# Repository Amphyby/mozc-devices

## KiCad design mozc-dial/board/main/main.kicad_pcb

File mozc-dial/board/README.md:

# Board Assembly Guide

For the entire keyboard assembly, please refer to the [Build Guide](../buildguide.md).

## Common to All Editions

### Sensor Board (per board)

#### Bill of Materials

| Ref | Description | Qty | Notes |
|---|---|---|---|
| R1,R3,R5 | Resistor 330Ω | 3 | Through-hole or surface-mount |
| R2,R4,R6 | Not populated | - | |
| U1-3 | Reflective photo sensor RPR-220 | 3 | (e.g., [Reflective Photo Sensor (Photoreflector) RPR-220](https://akizukidenshi.com/catalog/g/g111401/)) |
| J1 | 2.54mm pitch 1x5 pin header | 1 | L-shaped is desirable (e.g., [Pin Header (Male L-type) 1x40 (40P)](https://akizukidenshi.com/catalog/g/g101627/)) |

#### Assembly

This explanation covers the case where all 3 bits are populated. However, for the 9-dial edition, some sensors may only require 1 or 2 bits. In that case, populate only the required number of components from the top (U1). For details, follow the instructions for the 9-dial edition.

Also, before making everything, it is recommended to check if the Gray code plate values can be read properly to reduce rework in case of problems. If it doesn't work well, populate resistors on R2, R4, and R6. For details, see [Reading Sensor Adjustment](#reading-sensor-adjustment).

First, attach the photo sensors from the side where the U1, U2, and U3 markings are visible. Pay close attention to the orientation. The upper right corner is chamfered, so check the marking and the shape of the sensor to ensure they are in the same orientation. After correct placement, cut off the excess leads from the back and solder them.

On the back side, there are places to attach three resistors on the `(SENSOR)` side and three on the `(LED)` side, as shown in the figure. Both through-hole and chip resistors can be used, so use the parts of your choice. However, even for through-hole types, it is more stable to mount them without passing them through the holes when attaching the dial.

As for the resistors, it depends on the adjustment as mentioned above. By default, we recommended using the internal pull-up, leaving the `(SENSOR)` side unpopulated and installing a 330Ω resistor on the `(LED)` side. However, since the internal resistance value varies greatly from device to device, we now recommend using the `no_pull` variant of the firmware, with 33KΩ on the `(SENSOR)` side and 330Ω on the `(LED)` side.

For the 1x5 pin header, using an L-shaped one will fit well in the case.

During assembly, pay attention to the `⇧Center` mark. The inner circumference of the dial will be in the direction of the arrow.

## 1-Dial Edition

This is an introductory edition that uses commercially available general-purpose parts other than the sensor board.

### Parts

- Raspberry Pi Pico: 1
- Sensor board (3-bit populated): 2
- [Unipolar Stepping Motor 28BYJ-48 5V](https://akizukidenshi.com/catalog/g/g113256/): 1
- [Stepping Motor Drive Module [M2003S]](https://www.aitendo.com/product/12366): 1
- Wiring materials: as needed

### Assembly

#### Sensor Board

Assemble two 3-bit populated sensor boards as described in the common section for all dial editions. We will call one `SENSOR L` and the other `SENSOR H`.

Although not a clean example as it was used for experiments, here are examples of mounting both through-hole and chip resistors.

Each board's pin header has five terminals: `V`, `1`, `2`, `3`, and `G`.
Of these, `V` connects to the 3.3V power supply, but the Raspberry Pi Pico we are using has only one 3.3V output terminal. Therefore, connect the terminal pair where `V` passes on the board, as shown by the red wiring in the photo.
In the diagram for the sensor board, the terminals inside the rectangle labeled `V`, that is, the six outer locations of the resistor patterns, are `V`.

The upper sensor board is `SENSOR L` for the inner circumference, and the lower sensor board is `SENSOR H` for the outer circumference.
Since `V` is interconnected, the `V` at the top-most, inner-most terminal is not needed for this connection.

#### Stepping Motor Drive Module

The Raspberry Pi Pico's GPIO cannot drive the motor directly, so the 1-dial edition uses a commercially available drive module. Any sink-type driver other than the one specified here will work, and you can also build your own by referring to the circuit of the 9-dial edition.

Taking the one mentioned here as an example, `IN1` to `IN4` enclosed in green are the terminals that receive the outputs `1` to `4` from the Raspberry Pi Pico. `GND` enclosed in black and `VCC` enclosed in red are `G` and `V` respectively.
The motor draws 5V power from the USB bus via the Raspberry Pi Pico. It requires about 0.3A, so the firmware for the 1-dial edition requests the 0.5A upper limit for USB micro.

The white terminal is used for connection with the stepping motor.

#### Raspberry Pi Pico

Attach L-shaped pin headers to a commercially available Raspberry Pi Pico as shown in the photo.
The three DEBUG pins at the bottom of the photo are optional and only needed if you need to develop and debug the firmware.

The pins used in the 1-dial edition are assigned as shown in the diagram. Connect to SENSOR L, SENSOR H, and MOTOR according to this diagram. When debugging, the standard output is output from TX via UART.

### Firmware Flashing

Follow the general method for the Raspberry Pi Pico. Connect the Raspberry Pi Pico to your PC while holding down the `BOOT` button on the board. A drive named `RPI-RP2` will appear. Copy `firmware/prebuilt/one_dial.uf2` into this drive. If the flashing is successful, the drive will disappear. Your OS may show a warning, but this is not a problem. From now on, when you connect this device to your PC without holding down the `BOOT` button, it will be recognized as a USB keyboard.

## 9-Dial Edition

### Parts

- Main board: 1
- Sensor board (3-bit populated): 6
- Sensor board (2-bit populated): 4
- Sensor board (1-bit populated): 1
- [Unipolar Stepping Motor 28BYJ-48 5V](https://akizukidenshi.com/catalog/g/g113256/): 9
- Wiring materials: as needed

### Main Board

#### Bill of Materials

| Ref | Description | Qty | Notes |
|---|---|---|---|
| C101 | Capacitor 10uF | 1 | |
| C102-121,C202-208,C212,C302-308,C312 | Capacitor 100nF | 36 | |
| C201,C209,C301,C309 | Capacitor 1uF | 4 | |
| C210,C211,C310,C311 | Capacitor 20pF | 4 | |
| J102-103 | 2.54mm pitch 1x3 pin header | 2 | |
| J106-J125 | 2.54mm pitch 1x5 pin header | 20 | |
| J201,J301 | USB TYPE C Receptacle | 2 | |
| R201-202,R301-302 | Resistor 27.4Ω | 4 | |
| R203-204,R303-304 | Resistor 5.1KΩ | 4 | |
| R205,R207,R305,R307 | Resistor 1KΩ | 4 | |
| R206,R306 | Resistor 10KΩ | 2 | |
| SW101,SW201,SW301 | Switch | 3 | |
| U101 | AMS1117 3.3V Regulator | 1 | |
| U102-103,U105,U107,U109 | TBD62083AFNG | 5 | |
| U104,U106,U108,U110 | 74HC238 | 4 | |
| U201,U301 | RP2040 | 2 | |
| U202,U302 | W25Q128JVS | 2 | |
| Y201,Y301 | 12MHz Crystal Oscillator | 2 | |
| N/A | Jumper pin | 2 | |

#### Assembly

The Gerber data for the main board is in `board/gerber/main.zip`. Together with `main_bom.csv` and `main_positions.csv`, this data can be used to order board manufacturing and assembly from JLCPCB. If you order correctly, you will receive a semi-finished board like the one below.

### Assembly

Attach 1x5 L-shaped pin headers for connecting to the sensor boards to `SENSOR A-L`, `SENSOR A-H`, `SENSOR B`, `SENSOR C`, `SENSOR D`, `SENSOR E`, `SENSOR F`, `SENSOR G`, `SENSOR H`, `SENSOR I-L`, and `SENSOR I-H`.

Attach 1x5 L-shaped pin headers for connecting to the motors to `MOTOR A`, `MOTOR B`, `MOTOR C`, `MOTOR D`, `MOTOR E`, `MOTOR F`, `MOTOR G`, `MOTOR H`, and `MOTOR I`.

If you attach them facing outwards on the front side like this, it will be easier to route the cables during wiring. It is a good idea to not insert the inner pins all the way, but to leave them slightly raised to create a height difference. Be especially careful with `SENSOR I-H`, which will pass over the USB connector.

The following work on the back side can minimize the board thickness and at the same time avoid short circuits with components and heat dissipation problems.

Attach a 1x3 pin header to the location marked `U1 PWR U2` and short the `U1` and `PWR` positions with a jumper pin.

Attach a 1x3 pin header to the location marked `USB V_MTR ALT` and short the `USB` and `V_MTR` positions with a jumper pin.

### Sensor Board

Referring to the [Common to All Dial Editions](#common-to-all-dial-editions) section, prepare a total of 11 sensor boards with the following populated bit widths. There is no problem other than an increase in standby power consumption if you populate more bits, so it is also fine to prepare all of them with a 3-bit width.

| Ref | Populated Bit Width |
|---|---|
| SENSOR A-L | 3 |
| SENSOR A-H | 3 |
| SENSOR B | 2 |
| SENSOR C | 3 |
| SENSOR D | 2 |
| SENSOR E | 3 |
| SENSOR F | 3 |
| SENSOR G | 2 |
| SENSOR H | 2 |
| SENSOR I-L | 3 |
| SENSOR I-H | 1 |

### Firmware Flashing

This dedicated board also follows the general method for Raspberry Pi Pico, but since two RP2040s are mounted on the board, you need to flash two firmwares to each.

First, flash the sub-chip using the USB Type-C terminal labeled `USB 2`. The jumper labeled `U1 PWR U2` normally shorts `U1` and `PWR`. This is a setting where the power on the board is taken from the `USB 1` terminal. Temporarily change this to short `PWR` and `U2`.

In this state, connect the `USB 2` terminal to the PC while holding down `BOOT 2`. Copy `sub.uf2` or `sub_no_pull.uf2` to the drive named `RPI-RP2` that appears on the PC. If the writing is successful, the drive will disappear.

Once disconnect from the PC, and then flash the main firmware. Return the jumper setting to shorting `U1` and `PWR`, and connect the `USB 1` terminal to the PC while holding down `BOOT 1`. Similarly, copy `main.uf2` or `main_no_pull.uf2`. When the drive disappears, the flashing is complete.

## Photo Sensor Adjustment

The photo sensor readings should not vary greatly as they are taken inside the case, but differences may arise due to the brightness of the 3D printing material or the quality of the paper on which the Gray code is printed. If the dial reading is unstable or the rotation does not stop, the sensor value change range may not be within the expected range. In that case, please adjust the sensor paying attention to the following points.

### Reading with RP2040

The sensor value is processed as a digital value by GPIO. Therefore, it needs to be adjusted so that HIGH is in the range of 2.0 - 3.3[V] and LOW is in the range of 0.0 - 0.3[V] when operating at 3.3V.

### LED Sensor Adjustment

If the current flowing through the LED is small, the light emission will be weak, and the amount of light read by the sensor will be insufficient. This will result in higher readings, and the voltage difference between white and black will not be clear. In that case, try changing the three resistors on the `(LED)` side to weaker ones. The standard is adjusted with 330Ω, but with the photo sensor RPR-220 used this time, it will stay within the rated value even if you lower it to about 40Ω. However, it will greatly affect the standby power consumption, so if possible, please adjust with the resistor on the reading sensor side.

### Reading Sensor Adjustment

You can shift the read voltage value by changing the pull-up resistance of the reading sensor. However, if you change it too much, the voltage difference between white and black will become less clear. You can adjust it by populating the three resistors on the `(SENSOR)` side. The standard firmware expects a pull-up of about 50-80KΩ by the RP2040's pull-up. If the voltage does not rise sufficiently with black, it is better to pull-up more strongly with an additional resistor. By following the [Firmware Development Guide](../firmware/README.md) and disabling the RP2040's pull-up, the resistor populated here will become the pull-up resistor. If you do not disable it, it will be pulled up by the combined resistance in parallel. The calculation is a bit complicated, but it may be easier to pull-up in parallel with an additional resistor without changing the firmware if you want to pull-up more strongly.

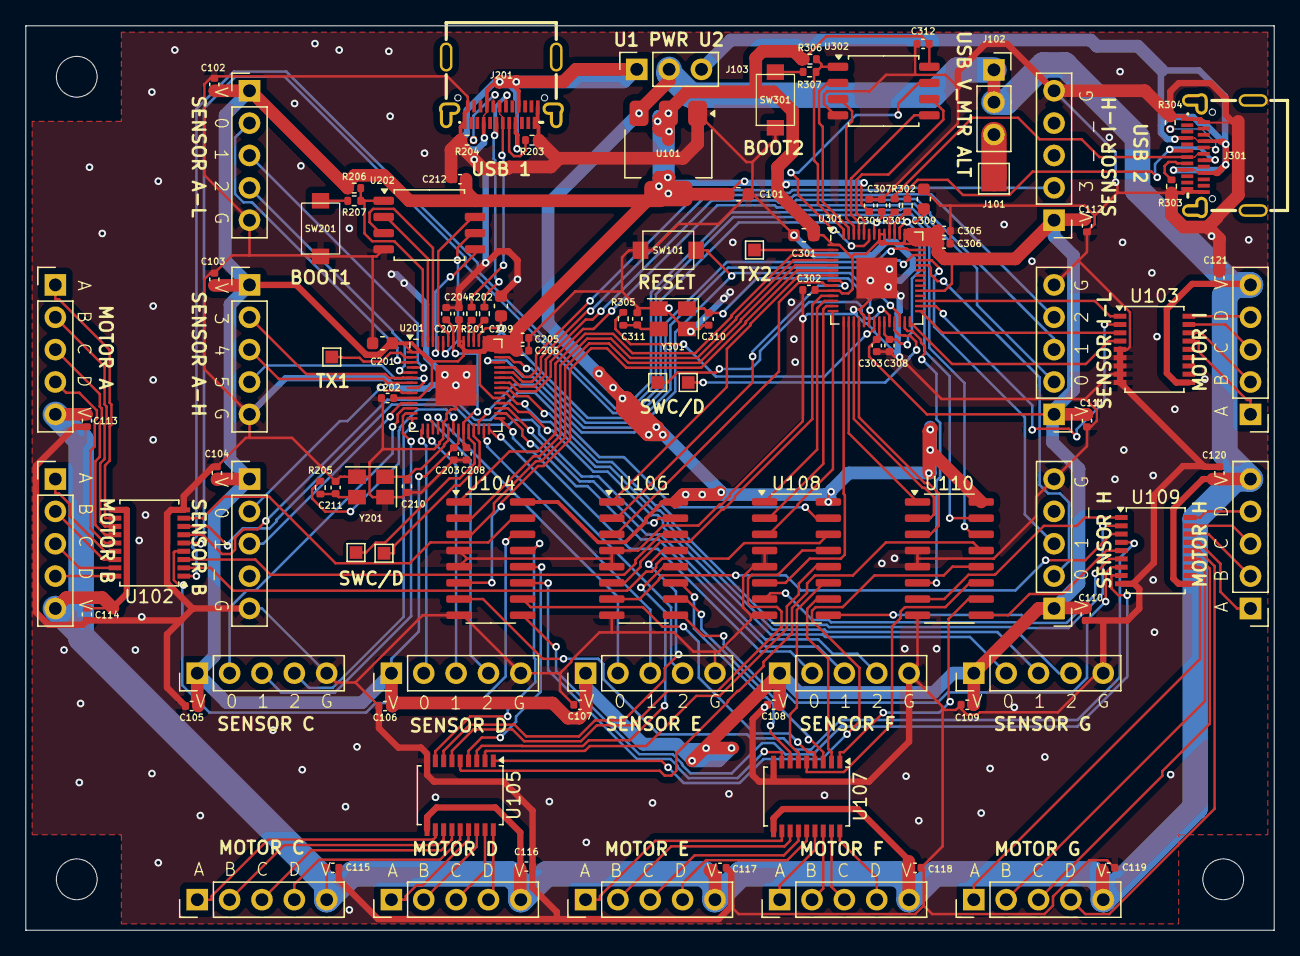
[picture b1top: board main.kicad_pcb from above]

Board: 2 copper layers, 98.0 x 71.0 mm, 112 parts (0 on the bottom side), 165 nets.

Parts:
C101: 10u; C_0603_1608Metric
C102, C103, C104, C105, C106, C107, C108, C109, C110, C111, C112, C113, C114, C115, C116, C117, C118, C119, C120, C121, C202, C203, C204, C205, C206, C207, C208, C212, C302, C303, C304, C305, C306, C307, C308, C312: 100n; C_0402_1005Metric
C201, C209, C301, C309: 1u; C_0603_1608Metric
C210, C211, C310, C311: 20p; C_0402_1005Metric
J101: Conn_01x01; TestPoint_Pad_2.0x2.0mm
J102, J103: Conn_01x03; PinSocket_1x03_P2.54mm_Vertical
J104, J105, J202, J203, J302, J303: Conn_01x01; TestPoint_Pad_1.0x1.0mm
J106, J107, J108, J109, J110, J111, J112, J113, J114, J115, J116, J117, J118, J119, J120, J121, J122, J123, J124, J125: Conn_01x05_Pin; PinHeader_1x05_P2.54mm_Vertical
J201, J301: USB_C_Receptacle; USBC_24P
R201, R202, R301, R302: 27.4; R_0402_1005Metric
R203, R204, R303, R304: 5.1K; R_0402_1005Metric
R205, R207, R305, R307: 1K; R_0402_1005Metric
R206, R306: 10K; R_0402_1005Metric
REF1, REF2, REF3: MountingHole_3.2mm_M3
SW101, SW201, SW301: SW_Push; SW_SMD_PUSH
U101: AMS1117-3.3; SOT-223-3_TabPin2
U102, U103, U105, U107, U109: TBD62083AFNG; SSOP-18_4.4x6.5mm_P0.65mm
U104, U106, U108, U110: 74HC238; SOP-16_3.9x9.9mm_P1.27mm
U201, U301: RP2040; QFN-56-1EP_7x7mm_P0.4mm_EP3.2x3.2mm
U202, U302: W25Q128JVS; SOIC-8_5.3x5.3mm_P1.27mm
Y201, Y301: 12MHz_GND24; Crystal_SMD_SeikoEpson_TSX3225-4Pin_3.2x2.5mm

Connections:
+1V1: C207.1, C208.1, C209.1, C307.1, C308.1, C309.1, U201.23 (DVDD), U201.45 (VREG_VOUT), U201.50 (DVDD), U301.23 (DVDD), U301.45 (VREG_VOUT), U301.50 (DVDD)
+3V3: C101.1, C102.1, C103.1, C104.1, C105.1, C106.1, C107.1, C108.1, C109.1, C110.1, C111.1, C112.1, C201.1, C202.1, C203.1, C204.1, C205.1, C206.1, C212.1, C301.1, C302.1, C303.1, C304.1, C305.1, C306.1, C312.1, J114.1, J115.1, J116.1, J117.1, J118.1, J120.1, J121.1, J122.1, J123.1, J124.1, J125.1, R206.1, R306.1, U101.2 (VO), U201.1 (IOVDD), U201.10 (IOVDD), U201.22 (IOVDD), U201.33 (IOVDD), U201.42 (IOVDD), U201.43 (ADC_AVDD), U201.44 (VREG_IN), U201.48 (USB_VDD), U201.49 (IOVDD), U202.8 (VCC), U301.1 (IOVDD), U301.10 (IOVDD), U301.22 (IOVDD), U301.33 (IOVDD), U301.42 (IOVDD), U301.43 (ADC_AVDD), U301.44 (VREG_IN), U301.48 (USB_VDD), U301.49 (IOVDD), U302.8 (VCC)
+5V: C113.1, C114.1, C115.1, C116.1, C117.1, C118.1, C119.1, C120.1, C121.1, J102.1, J102.2, J103.2, J106.5, J107.5, J108.5, J109.5, J110.5, J111.5, J112.5, J113.5, J119.5, U101.3 (VI), U102.10 (COMMON), U103.10 (COMMON), U104.16 (VCC), U105.10 (COMMON), U106.16 (VCC), U107.10 (COMMON), U108.16 (VCC), U109.10 (COMMON), U110.16 (VCC)
/I2C_SCL: U201.41 (GPIO29_ADC3), U301.41 (GPIO29_ADC3)
/I2C_SDA: U201.40 (GPIO28_ADC2), U301.40 (GPIO28_ADC2)
/MTRA_0: U102.8 (I8), U104.15 (Y0)
/MTRA_1: U102.4 (I4), U104.14 (Y1)
/MTRA_2: U104.13 (Y2), U105.8 (I8)
/MTRA_3: U104.12 (Y3), U105.4 (I4)
/MTRA_4: U104.11 (Y4), U107.8 (I8)
/MTRA_5: U104.10 (Y5), U107.4 (I4)
/MTRA_6: U104.9 (Y6), U109.8 (I8)
/MTRA_7: U104.7 (Y7), U109.4 (I4)
/MTRA_8: U103.4 (I4), U301.28 (GPIO17)
/MTRB_0: U102.7 (I7), U106.15 (Y0)
/MTRB_1: U102.3 (I3), U106.14 (Y1)
/MTRB_2: U105.7 (I7), U106.13 (Y2)
/MTRB_3: U105.3 (I3), U106.12 (Y3)
/MTRB_4: U106.11 (Y4), U107.7 (I7)
/MTRB_5: U106.10 (Y5), U107.3 (I3)
/MTRB_6: U106.9 (Y6), U109.7 (I7)
/MTRB_7: U106.7 (Y7), U109.3 (I3)
/MTRB_8: U103.3 (I3), U301.29 (GPIO18)
/MTRC_0: U102.6 (I6), U108.15 (Y0)
/MTRC_1: U102.2 (I2), U108.14 (Y1)
/MTRC_2: U105.6 (I6), U108.13 (Y2)
/MTRC_3: U105.2 (I2), U108.12 (Y3)
/MTRC_4: U107.6 (I6), U108.11 (Y4)
/MTRC_5: U107.2 (I2), U108.10 (Y5)
/MTRC_6: U108.9 (Y6), U109.6 (I6)
/MTRC_7: U108.7 (Y7), U109.2 (I2)
/MTRC_8: U103.2 (I2), U301.30 (GPIO19)
/MTRD_0: U102.5 (I5), U110.15 (Y0)
/MTRD_1: U102.1 (I1), U110.14 (Y1)
/MTRD_2: U105.5 (I5), U110.13 (Y2)
/MTRD_3: U105.1 (I1), U110.12 (Y3)
/MTRD_4: U107.5 (I5), U110.11 (Y4)
/MTRD_5: U107.1 (I1), U110.10 (Y5)
/MTRD_6: U109.5 (I5), U110.9 (Y6)
/MTRD_7: U109.1 (I1), U110.7 (Y7)
/MTRD_8: U103.1 (I1), U301.31 (GPIO20)
/RESET: SW101.2, U201.26 (RUN), U301.26 (RUN)
/RP2040_1/QSPI_SCLK: U201.52 (QSPI_SCLK), U202.6 (CLK)
/RP2040_1/QSPI_SD0: U201.53 (QSPI_SD0), U202.5 (DI/IO_{0})
/RP2040_1/QSPI_SD1: U201.55 (QSPI_SD1), U202.2 (DO/IO_{1})
/RP2040_1/QSPI_SD2: U201.54 (QSPI_SD2), U202.3 (~WP/IO_{2})
/RP2040_1/QSPI_SD3: U201.51 (QSPI_SD3), U202.7 (~HOLD/~RESET/IO_{3})
/RP2040_1/QSPI_SS: R206.2, R207.2, U201.56 (QSPI_SS), U202.1 (~CS)
/RP2040_1/SWCLK: J202.1, U201.24 (SWCLK)
/RP2040_1/SWD: J203.1, U201.25 (SWD)
/RP2040_1/USB_DM: J201.A7 (D-), J201.B7 (D-), R202.1
/RP2040_1/USB_DP: J201.A6 (D+), J201.B6 (D+), R201.1
/RP2040_1/VBUS: J103.1, J201.A4 (VBUS), J201.A9 (VBUS), J201.B4 (VBUS), J201.B9 (VBUS)
/RP2040_2/QSPI_SCLK: U301.52 (QSPI_SCLK), U302.6 (CLK)
/RP2040_2/QSPI_SD0: U301.53 (QSPI_SD0), U302.5 (DI/IO_{0})
/RP2040_2/QSPI_SD1: U301.55 (QSPI_SD1), U302.2 (DO/IO_{1})
/RP2040_2/QSPI_SD2: U301.54 (QSPI_SD2), U302.3 (~WP/IO_{2})
/RP2040_2/QSPI_SD3: U301.51 (QSPI_SD3), U302.7 (~HOLD/~RESET/IO_{3})
/RP2040_2/QSPI_SS: R306.2, R307.2, U301.56 (QSPI_SS), U302.1 (~CS)
/RP2040_2/SWCLK: J302.1, U301.24 (SWCLK)
/RP2040_2/SWD: J303.1, U301.25 (SWD)
/RP2040_2/USB_DM: J301.A7 (D-), J301.B7 (D-), R302.1
/RP2040_2/USB_DP: J301.A6 (D+), J301.B6 (D+), R301.1
/RP2040_2/VBUS: J103.3, J301.A4 (VBUS), J301.A9 (VBUS), J301.B4 (VBUS), J301.B9 (VBUS)
/SELA_0: U104.1 (A0), U301.3 (GPIO1)
/SELA_1: U104.2 (A1), U301.4 (GPIO2)
/SELA_2: U104.3 (A2), U301.5 (GPIO3)
/SELA_3: U104.6 (E3), U301.6 (GPIO4)
/SELB_0: U106.1 (A0), U301.7 (GPIO5)
/SELB_1: U106.2 (A1), U301.8 (GPIO6)
/SELB_2: U106.3 (A2), U301.9 (GPIO7)
/SELB_3: U106.6 (E3), U301.11 (GPIO8)
/SELC_0: U108.1 (A0), U301.12 (GPIO9)
/SELC_1: U108.2 (A1), U301.13 (GPIO10)
/SELC_2: U108.3 (A2), U301.14 (GPIO11)
/SELC_3: U108.6 (E3), U301.15 (GPIO12)
/SELD_0: U110.1 (A0), U301.16 (GPIO13)
/SELD_1: U110.2 (A1), U301.17 (GPIO14)
/SELD_2: U110.3 (A2), U301.18 (GPIO15)
/SELD_3: U110.6 (E3), U301.27 (GPIO16)
/SINK0_A: J106.1, U102.11 (O8)
/SINK0_B: J106.2, U102.12 (O7)
/SINK0_C: J106.3, U102.13 (O6)
/SINK0_D: J106.4, U102.14 (O5)
/SINK1_A: J108.1, U102.15 (O4)
/SINK1_B: J108.2, U102.16 (O3)
/SINK1_C: J108.3, U102.17 (O2)
/SINK1_D: J108.4, U102.18 (O1)
/SINK2_A: J110.1, U105.11 (O8)
/SINK2_B: J110.2, U105.12 (O7)
/SINK2_C: J110.3, U105.13 (O6)
/SINK2_D: J110.4, U105.14 (O5)
/SINK3_A: J112.1, U105.15 (O4)
/SINK3_B: J112.2, U105.16 (O3)
/SINK3_C: J112.3, U105.17 (O2)
/SINK3_D: J112.4, U105.18 (O1)
/SINK4_A: J119.1, U107.11 (O8)
/SINK4_B: J119.2, U107.12 (O7)
/SINK4_C: J119.3, U107.13 (O6)
/SINK4_D: J119.4, U107.14 (O5)
/SINK5_A: J107.1, U107.15 (O4)
/SINK5_B: J107.2, U107.16 (O3)
/SINK5_C: J107.3, U107.17 (O2)
/SINK5_D: J107.4, U107.18 (O1)
/SINK6_A: J109.1, U109.11 (O8)
/SINK6_B: J109.2, U109.12 (O7)
/SINK6_C: J109.3, U109.13 (O6)
/SINK6_D: J109.4, U109.14 (O5)
/SINK7_A: J111.1, U109.15 (O4)
/SINK7_B: J111.2, U109.16 (O3)
/SINK7_C: J111.3, U109.17 (O2)
/SINK7_D: J111.4, U109.18 (O1)
/SINK8_A: J113.1, U103.15 (O4)
/SINK8_B: J113.2, U103.16 (O3)
/SINK8_C: J113.3, U103.17 (O2)
/SINK8_D: J113.4, U103.18 (O1)
/SNSA_0: J114.2, U201.3 (GPIO1)
/SNSA_1: J114.3, U201.4 (GPIO2)
/SNSA_2: J114.4, U201.5 (GPIO3)
/SNSA_3: J118.2, U201.6 (GPIO4)
/SNSA_4: J118.3, U201.7 (GPIO5)
/SNSA_5: J118.4, U201.8 (GPIO6)
/SNSB_0: J115.2, U201.9 (GPIO7)
/SNSB_1: J115.3, U201.11 (GPIO8)
/SNSC_0: J116.2, U201.12 (GPIO9)
/SNSC_1: J116.3, U201.13 (GPIO10)
/SNSC_2: J116.4, U201.14 (GPIO11)
/SNSD_0: J117.2, U201.15 (GPIO12)
/SNSD_1: J117.3, U201.16 (GPIO13)
/SNSD_2: J117.4, U201.17 (GPIO14)
/SNSE_0: J121.2, U201.18 (GPIO15)
/SNSE_1: J121.3, U201.27 (GPIO16)
/SNSE_2: J121.4, U201.28 (GPIO17)
/SNSF_0: J122.2, U201.29 (GPIO18)
/SNSF_1: J122.3, U201.30 (GPIO19)
/SNSF_2: J122.4, U201.31 (GPIO20)
/SNSG_0: J123.2, U201.32 (GPIO21)
/SNSG_1: J123.3, U201.34 (GPIO22)
/SNSG_2: J123.4, U201.35 (GPIO23)
/SNSH_0: J124.2, U301.38 (GPIO26_ADC0)
/SNSH_1: J124.3, U301.39 (GPIO27_ADC1)
/SNSI_0: J125.2, U201.36 (GPIO24)
/SNSI_1: J125.3, U201.37 (GPIO25)
/SNSI_2: J125.4, U201.38 (GPIO26_ADC0)
/SNSI_3: J120.2, U201.39 (GPIO27_ADC1)
/TX_1: J105.1, U201.2 (GPIO0)
/TX_2: J104.1, U301.2 (GPIO0)
/VBUS_ALT: J101.1, J102.3
GND: C101.2, C102.2, C103.2, C104.2, C105.2, C106.2, C107.2, C108.2, C109.2, C110.2, C111.2, C112.2, C113.2, C114.2, C115.2, C116.2, C117.2, C118.2, C119.2, C120.2, C121.2, C201.2, C202.2, C203.2, C204.2, C205.2, C206.2, C207.2, C208.2, C209.2, C210.1, C211.1, C212.2, C301.2, C302.2, C303.2, C304.2, C305.2, C306.2, C307.2, C308.2, C309.2, C310.1, C311.1, C312.2, J114.5, J115.5, J116.5, J117.5, J118.5, J120.5, J121.5, J122.5, J123.5, J124.5, J125.5, J201.A1 (GND), J201.A12 (GND), J201.B1 (GND), J201.B12 (GND), J301.A1 (GND), J301.A12 (GND), J301.B1 (GND), J301.B12 (GND), R203.2, R204.2, R303.2, R304.2, SW101.1, SW201.1, SW301.1, U101.1 (GND), U102.9 (GND), U103.5 (I5), U103.6 (I6), U103.7 (I7), U103.8 (I8), U103.9 (GND), U104.4 (~E1), U104.5 (~E2), U104.8 (GND), U105.9 (GND), U106.4 (~E1), U106.5 (~E2), U106.8 (GND), U107.9 (GND), U108.4 (~E1), U108.5 (~E2), U108.8 (GND), U109.9 (GND), U110.4 (~E1), U110.5 (~E2), U110.8 (GND), U201.19 (TESTEN), U201.57 (GND), U202.4 (GND), U301.19 (TESTEN), U301.57 (GND), U302.4 (GND), Y201.2, Y201.4, Y301.2, Y301.4
unnamed: C211.2, R205.1, Y201.3
unnamed: C311.2, R305.1, Y301.3
unnamed: J201.A5 (CC1), R203.1
unnamed: J201.B5 (CC2), R204.1
unnamed: J301.A5 (CC1), R303.1
unnamed: J301.B5 (CC2), R304.1
unnamed: R207.1, SW201.2
unnamed: R307.1, SW301.2
unnamed: R202.2, U201.46 (USB_DM)
unnamed: R201.2, U201.47 (USB_DP)
unnamed: C210.2, U201.20 (XIN), Y201.1
unnamed: R205.2, U201.21 (XOUT)
unnamed: R302.2, U301.46 (USB_DM)
unnamed: R301.2, U301.47 (USB_DP)
unnamed: C310.2, U301.20 (XIN), Y301.1
unnamed: R305.2, U301.21 (XOUT)

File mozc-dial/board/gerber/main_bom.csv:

Designator,Footprint,Quantity,Value,LCSC Part #
C101,0603,1,10u,
"C102, C103, C104, C105, C106, C107, C108, C109, C110, C111, C112, C113, C114, C115, C116, C117, C118, C119, C120, C121",0402,20,100n,
"C201, C209, C301, C309",0603,4,1u,
"C202, C203, C204, C205, C206, C207, C208, C212, C302, C303, C304, C305, C306, C307, C308, C312",0402,16,100n,
"C210, C211, C310, C311",0402,4,20p,
J101,TestPoint_Pad_2.0x2.0mm,1,Conn_01x01,
"J104, J105, J202, J203, J302, J303",TestPoint_Pad_1.0x1.0mm,6,Conn_01x01,
"J201, J301",USBC_24P,2,USB_C_Receptacle,C2681555
"R201, R202, R301, R302",0402,4,27.4,
"R203, R204, R303, R304",0402,4,5.1K,
"R205, R207, R305, R307",0402,4,1K,
"R206, R306",0402,2,10K,
"SW101, SW201, SW301",SW_SMD_PUSH,3,SW_Push,C720477
U101,SOT-223-3_TabPin2,1,AMS1117-3.3,C347222
"U102, U103, U105, U107, U109",SSOP-18_4.4x6.5mm_P0.65mm,5,TBD62083AFNG,C163229
"U104, U106, U108, U110",SOP-16_3.9x9.9mm_P1.27mm,4,74HC238,C7432189
"U201, U301",QFN-56-1EP_7x7mm_P0.4mm_EP3.2x3.2mm,2,RP2040,C2040
"U202, U302",SOIC-8_5.3x5.3mm_P1.27mm,2,W25Q128JVS,C97521
"Y201, Y301",Crystal_SMD_SeikoEpson_TSX3225-4Pin_3.2x2.5mm,2,12MHz_GND24,C9002

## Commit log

2025-10-06 Fix link text for Gboard Dial Version
2025-10-28 Add mozc-dial nine dial edition.
2025-11-07 Set background color to keymap.svg.
